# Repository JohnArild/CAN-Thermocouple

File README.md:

# CAN-Thermocouple
Work in progress! Not tested  
  
Simple device for converting thermocouple to CAN 2.0B.  
PCB design is ordered and will be tested when it arrives  
Based on [CANtest](https://github.com/JohnArild/CANtest).

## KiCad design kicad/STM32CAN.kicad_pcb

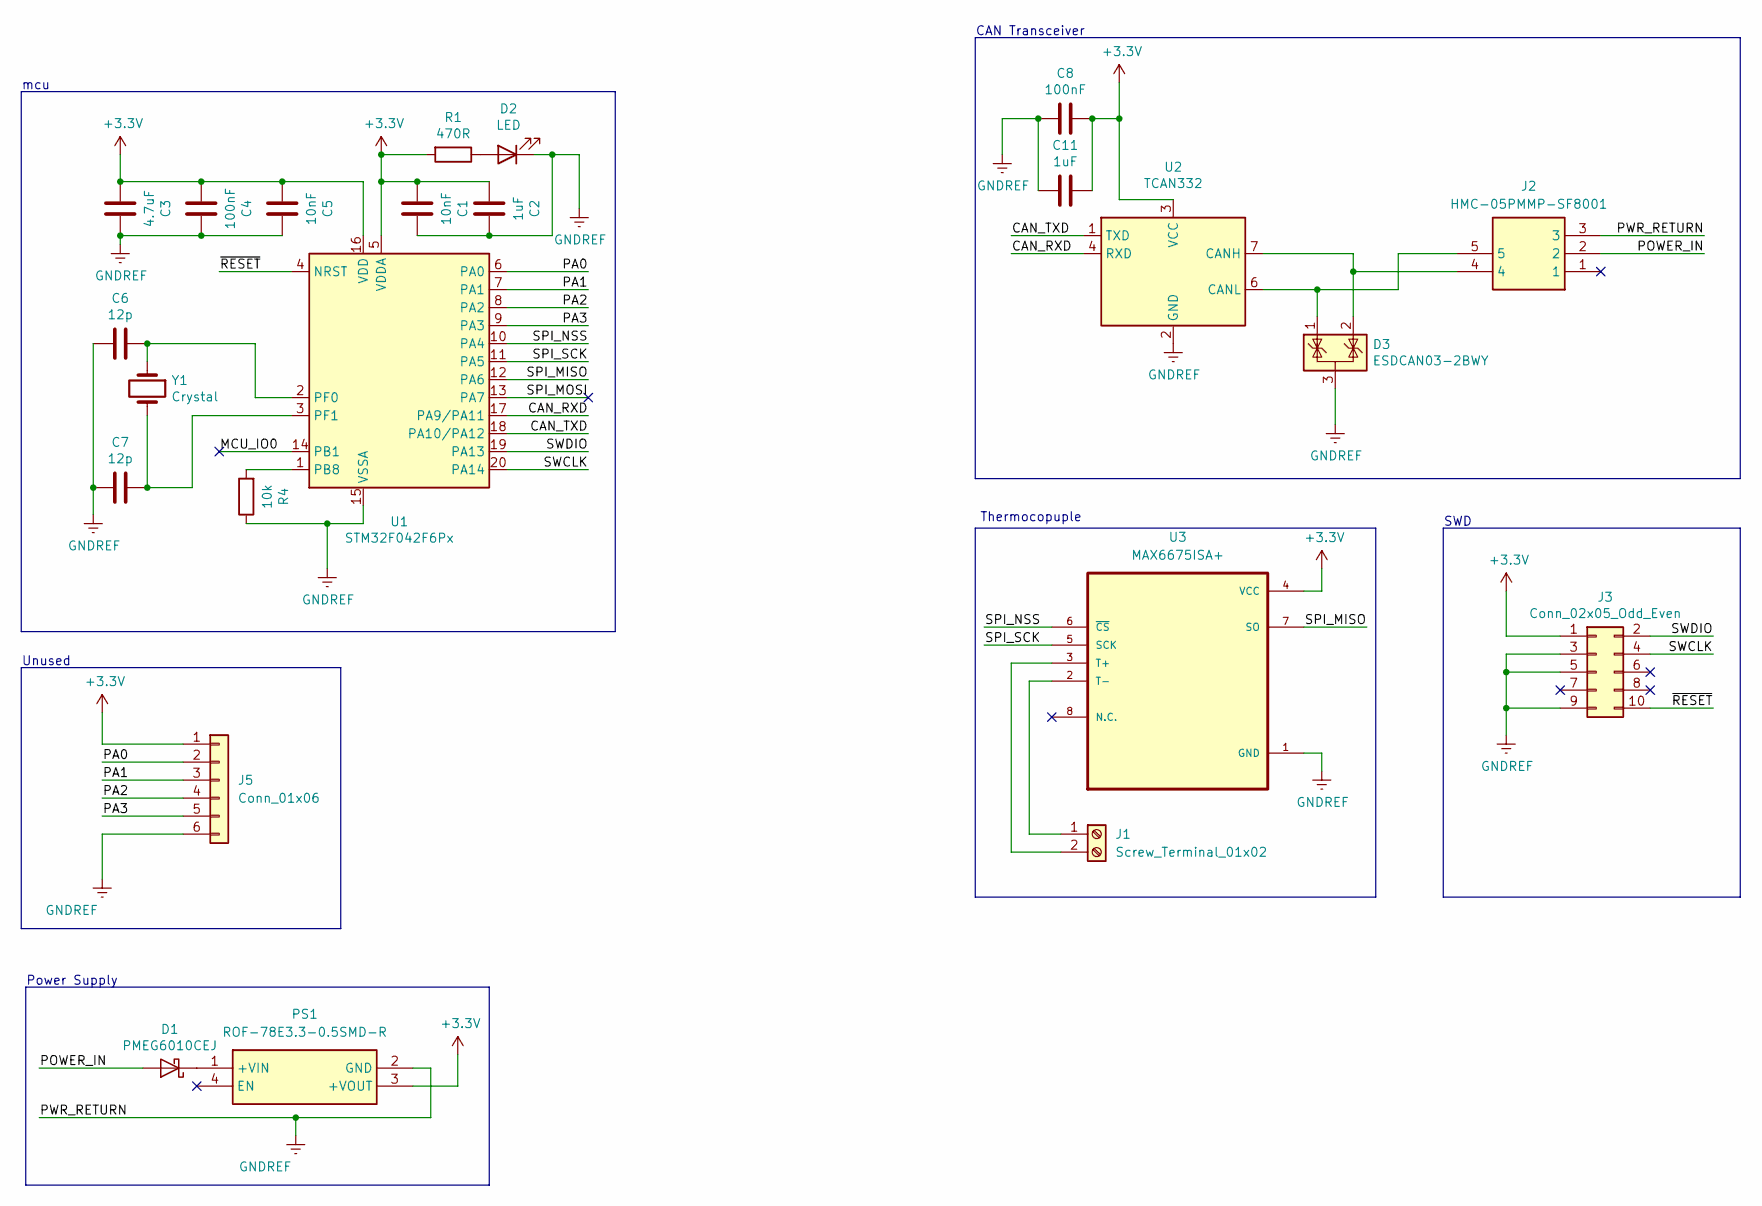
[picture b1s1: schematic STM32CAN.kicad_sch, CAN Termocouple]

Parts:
C1, C5: 10nF; C_0603_1608Metric
C2, C11: 1uF; C_0603_1608Metric
C3: 4.7uF; C_0603_1608Metric
C4, C8: 100nF; C_0603_1608Metric
C6, C7: 12p; C_0603_1608Metric
D1: PMEG6010CEJ; D_SOD-323
D2: LED; D_0603_1608Metric
D3: ESDCAN03-2BWY; SOT-323_SC-70
J1: Screw_Terminal_01x02; TerminalBlock_4Ucon_1x02_P3.50mm_Horizontal
J2: HMC-05PMMP-SF8001; HMC05PMMPSF8001; Mouser Part Number 523-HMC-05PMMPSF8001
J3: Conn_02x05_Odd_Even; PinHeader_2x05_P1.27mm_Vertical_SMD
J5: Conn_01x06; JST_XH_B6B-XH-A_1x06_P2.50mm_Vertical
PS1: ROF-78E3.3-0.5SMD-R; ROF78E3305SMDR; Mouser Part Number 919-ROF78E3.3-.5SMDR
R1: 470R; R_0603_1608Metric
R4: 10k; R_0603_1608Metric
U1: STM32F042F6Px; TSSOP-20_4.4x6.5mm_P0.65mm
U2: TCAN332; SOIC-8_3.9x4.9mm_P1.27mm
U3: MAX6675ISA+; SOIC127P600X175-8N
Y1: Crystal; 7A8000MAAET

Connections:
+3V3: C1.2, C2.2, C3.2, C4.2, C5.2, C8.1, C11.1, J3.1, J5.1, PS1.3 (+VOUT), R1.2, U1.5 (VDDA), U1.16 (VDD), U2.3 (VCC), U3.4 (VCC)
/CAN_RXD: U1.17 (PA9/PA11), U2.4 (RXD)
/CAN_TXD: U1.18 (PA10/PA12), U2.1 (TXD)
/MCU_IO0: U1.14 (PB1)
/PA0: J5.2, U1.6 (PA0)
/PA1: J5.3, U1.7 (PA1)
/PA2: J5.4, U1.8 (PA2)
/PA3: J5.5, U1.9 (PA3)
/POWER_IN: D1.2 (A), J2.2
/SPI_MISO: U1.12 (PA6), U3.7 (SO)
/SPI_MOSI: U1.13 (PA7)
/SPI_NSS: U1.10 (PA4), U3.6 (~CS)
/SPI_SCK: U1.11 (PA5), U3.5 (SCK)
/SWCLK: J3.4, U1.20 (PA14)
/SWDIO: J3.2, U1.19 (PA13)
/~RESET: J3.10, U1.4 (NRST)
GNDREF: C1.1, C2.1, C3.1, C4.1, C5.1, C6.2, C7.2, C8.2, C11.2, D2.1 (K), D3.3 (A), J2.3, J3.3, J3.5, J3.9, J5.6, PS1.2 (GND), R4.1, U1.15 (VSSA), U2.2 (GND), U3.1 (GND)
unnamed: D1.1 (K), PS1.1 (+VIN)
unnamed: D2.2 (A), R1.1
unnamed: J1.1, U3.2 (T-)
unnamed: J1.2, U3.3 (T+)
unnamed: R4.2, U1.1 (PB8)
unnamed: C6.1, U1.2 (PF0), Y1.1
unnamed: C7.1, U1.3 (PF1), Y1.2
unnamed: D3.2 (K), J2.4, U2.7 (CANH)
unnamed: D3.1 (K), J2.5, U2.6 (CANL)

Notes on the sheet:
mcu
Unused
CAN Transceiver
SWD
Power Supply
Thermocopuple

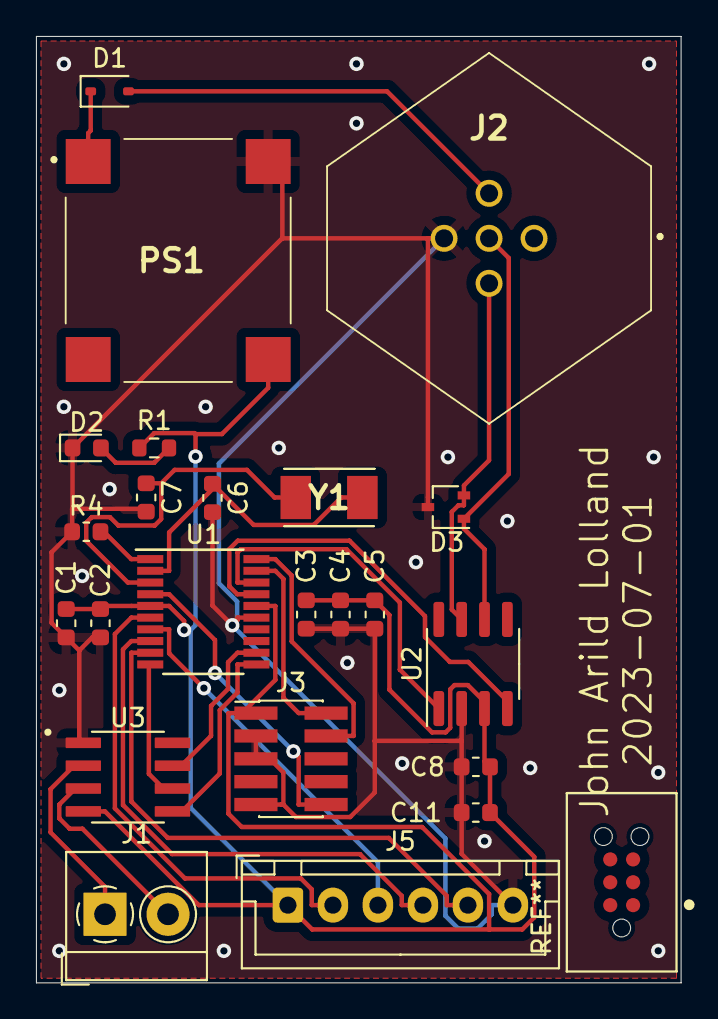
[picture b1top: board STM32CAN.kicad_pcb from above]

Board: 2 copper layers, 35.8 x 52.6 mm, 23 parts (0 on the bottom side), 24 nets.

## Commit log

2023-07-03 PCB ordered
